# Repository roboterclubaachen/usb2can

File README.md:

# usb2can: Compact, isolated USB to CAN Adaptor <span style="float:right;"></span>

USB2CAN is a compact, USB-based and isolated CAN adaptor.

It is based on

 * STM32F072 Crystal-less STM32F072 ARM Cortex-M0 Processor
 * ADM3053 Isolated CAN Transceiver

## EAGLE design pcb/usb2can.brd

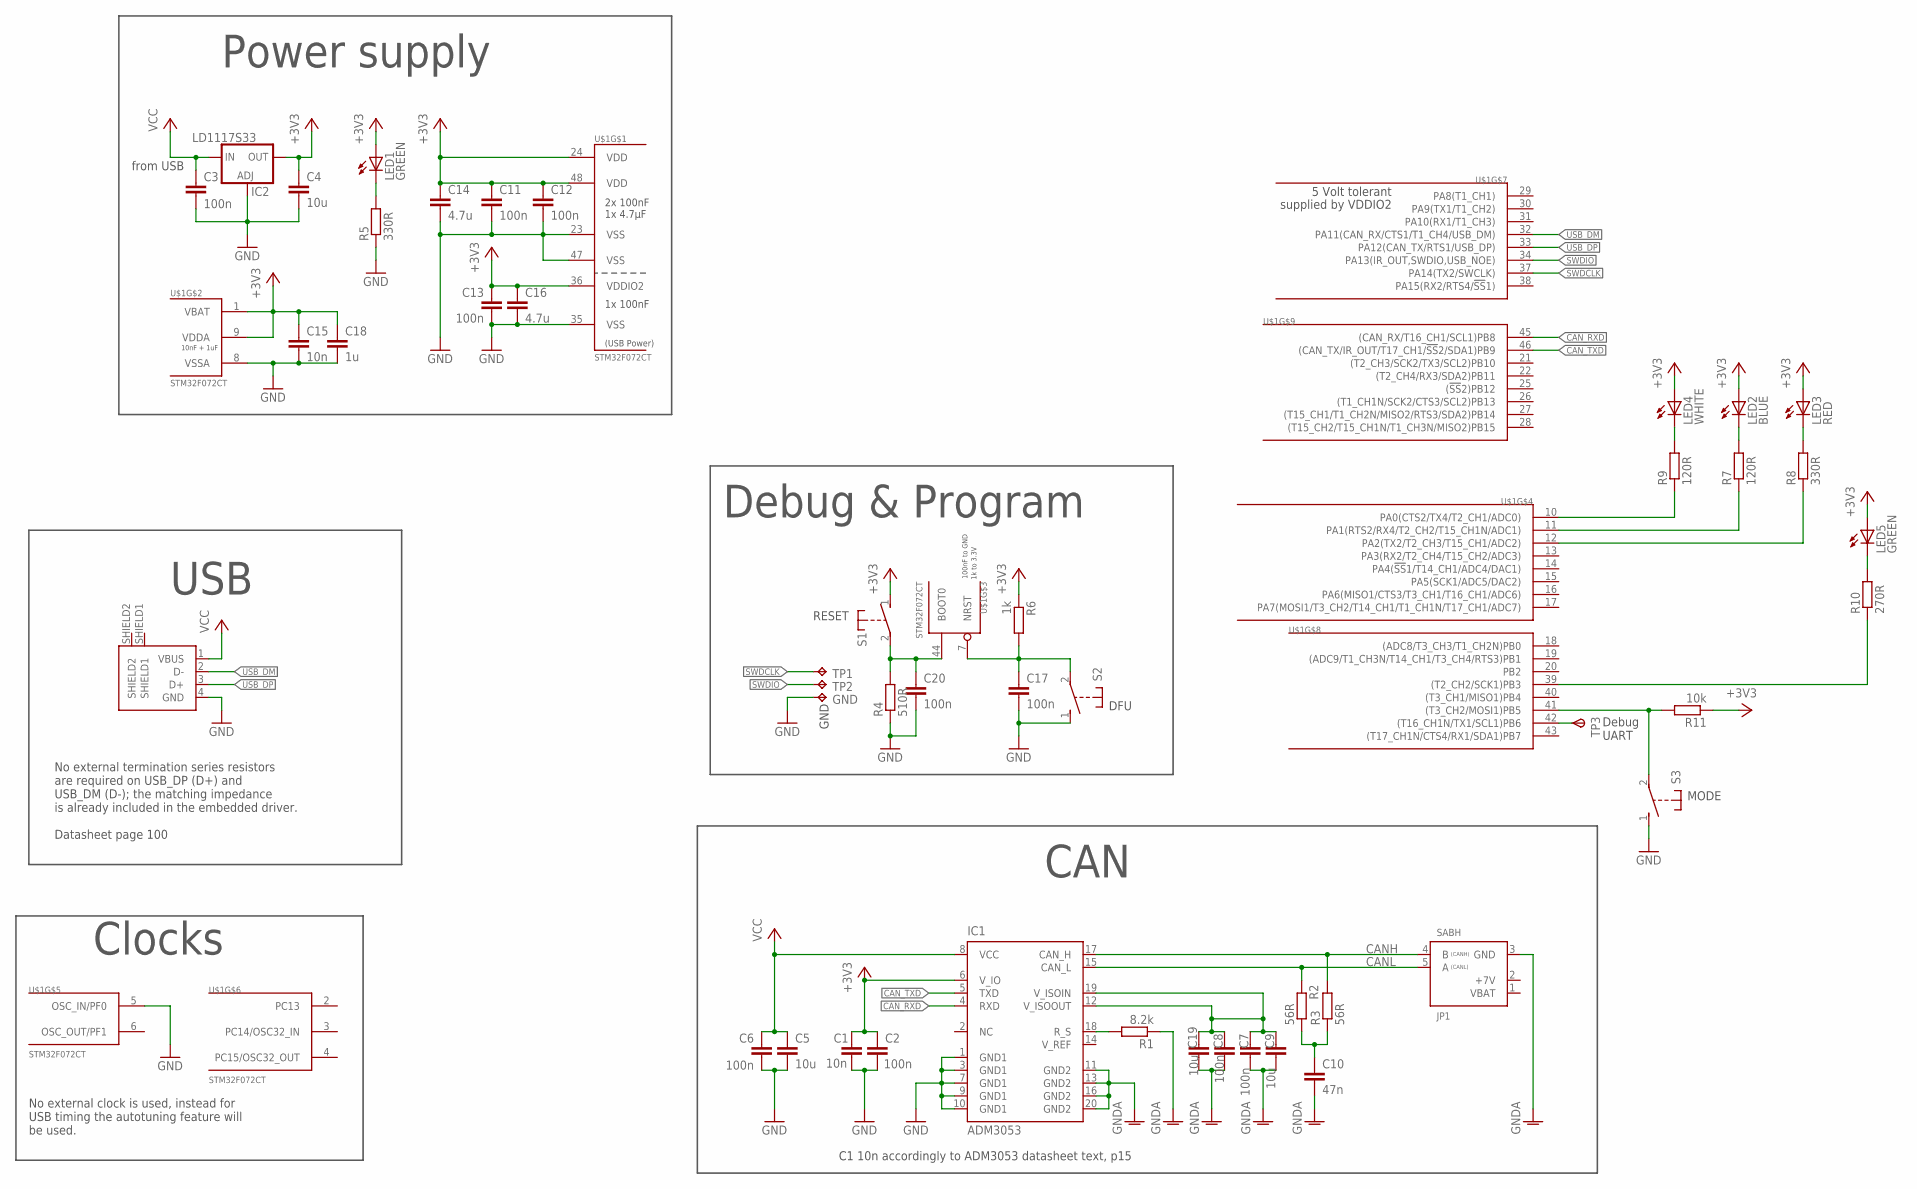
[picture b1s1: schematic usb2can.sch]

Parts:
C1: 10n; C0603K
C2, C3, C6: 100n; C0603K
C4, C5, C9, C19: 10u; C0805K
C7, C8: 100n; C0805K
C10: 47n; C0603K
C11, C12, C13, C17, C20: 100n; C0603
C14, C16: 4.7u; C0805K
C15: 10n; C0603
C18: 1u; C0805K
CON1: USB_A_MALESMD; USB_A_MALE_SMD
GND: TPB2,54; B2,54
IC1: ADM3053; SO20L
IC2: LD1117S33; SOT223
JP1: SABH; 7395-05
LED1, LED5: GREEN; CHIPLED_0603
LED2: BLUE; CHIPLED_0603
LED3: RED; CHIPLED_0603
LED4: WHITE; CHIPLED_0603
R1: 8.2k; R0603
R2, R3: 56R; R0805
R4: 510R; R0603
R5, R8: 330R; R0603
R6: 1k; R0603
R7, R9: 120R; R0603
R10: 270R; R0603
R11: 10k; R0603
S1, S2, S3: MICRO_SWITCH_3X6X2.5S; MICRO_SWITCH_3X6X2.5
TP1, TP2: TPB2,54; B2,54
TP3: TPSTP07R; TP07R
U$1: STM32F072CT; TQFP48

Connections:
+3V3: C1.1, C2.1, C4.1, C11.1, C12.1, C13.1, C14.1, C15.1, C16.1, C18.1, IC1.6 (V_IO), IC2.4 (OUT), LED1.A, LED2.A, LED3.A, LED4.A, LED5.A, R6.1, R11.1, S1.1, U$1.1 (VBAT), U$1.9 (VDDA), U$1.24 (VDD), U$1.36 (VDDIO2), U$1.48 (VDD)
CANH: IC1.17 (CAN_H), JP1.4 (B), R3.2
CANL: IC1.15 (CAN_L), JP1.5 (A), R2.2
CAN_RXD: IC1.4 (RXD), U$1.45 ((CAN_RX/T16_CH1/SCL1)PB8)
CAN_TXD: IC1.5 (TXD), U$1.46 ((CAN_TX/IR_OUT/T17_CH1/!SS!2/SDA1)PB9)
GND: C1.2, C2.2, C3.2, C4.2, C5.2, C6.2, C11.2, C12.2, C13.2, C14.2, C15.2, C16.2, C17.2, C18.2, C20.2, CON1.4 (GND), GND.TP, IC1.1 (GND1), IC1.3 (GND1), IC1.7 (GND1), IC1.9 (GND1), IC1.10 (GND1), IC2.1 (ADJ), R4.1, R5.1, S2.1, S3.1, U$1.5 (OSC_IN/PF0), U$1.8 (VSSA), U$1.23 (VSS), U$1.35 (VSS), U$1.47 (VSS)
GNDA: C7.2, C8.2, C9.2, C10.2, C19.2, IC1.11 (GND2), IC1.13 (GND2), IC1.16 (GND2), IC1.20 (GND2), JP1.3 (GND), R1.1
unnamed: IC1.18 (R_S), R1.2
unnamed: C10.1, R2.1, R3.1
unnamed: LED1.C, R5.2
unnamed: C20.1, R4.2, S1.2, U$1.44 (BOOT0)
unnamed: C17.1, R6.2, S2.2, U$1.7 (NRST)
unnamed: C7.1, C8.1, C9.1, C19.1, IC1.12 (V_ISOOUT), IC1.19 (V_ISOIN)
unnamed: LED2.C, R7.2
unnamed: R11.2, S3.2, U$1.41 ((T3_CH2/MOSI1)PB5)
unnamed: LED3.C, R8.2
unnamed: LED4.C, R9.2
unnamed: R9.1, U$1.10 (PA0(CTS2/TX4/T2_CH1/ADC0))
unnamed: R7.1, U$1.11 (PA1(RTS2/RX4/T2_CH2/T15_CH1N/ADC1))
unnamed: R8.1, U$1.12 (PA2(TX2/T2_CH3/T15_CH1/ADC2))
unnamed: LED5.C, R10.2
unnamed: R10.1, U$1.39 ((T2_CH2/SCK1)PB3)
SWDCLK: TP1.TP, U$1.37 (PA14(TX2/SWCLK))
SWDIO: TP2.TP, U$1.34 (PA13(IR_OUT,SWDIO,USB_NOE))
TX: TP3.TP, U$1.42 ((T16_CH1N/TX1/SCL1)PB6)
USB_DM: CON1.2 (D-), U$1.32 (PA11(CAN_RX/CTS1/T1_CH4/USB_DM))
USB_DP: CON1.3 (D+), U$1.33 (PA12(CAN_TX/RTS1/USB_DP))
VCC: C3.1, C5.1, C6.1, CON1.1 (VBUS), IC1.8 (VCC), IC2.3 (IN)

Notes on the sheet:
CAN
No external termination series resistors are required on USB_DP (D+) and USB_DM (D-); the matching impedance is already included in the embedded driver. Datasheet page 100
USB
Clocks
No external clock is used, instead for USB timing the autotuning feature will be used.
from USB
Power supply
Debug & Program
Debug UART
C1 10n accordingly to ADM3053 datasheet text, p15
DFU
RESET
MODE

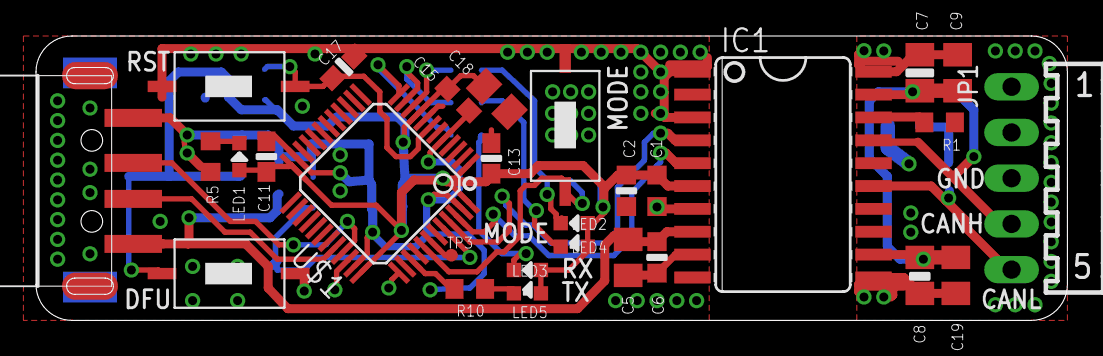
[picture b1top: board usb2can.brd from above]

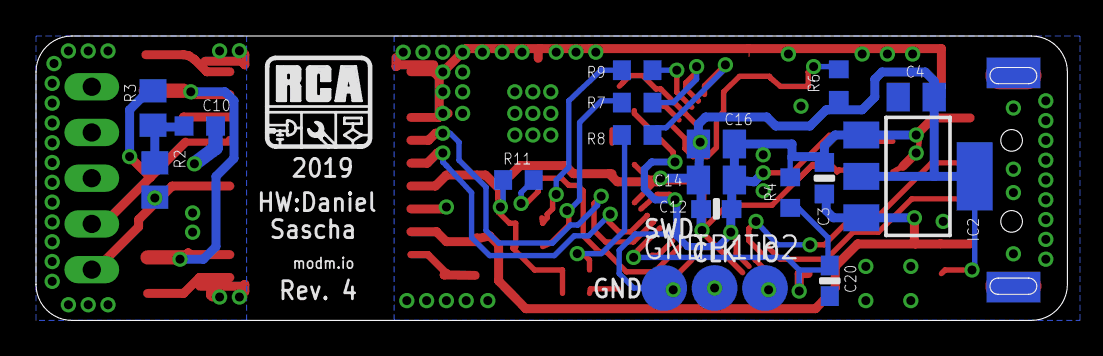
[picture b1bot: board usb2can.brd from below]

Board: 2 copper layers, 57.3 x 15.8 mm, 49 parts (19 on the bottom side), 28 nets.

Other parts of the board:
U$2: LOGO_SILK_BOT

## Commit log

2015-06-29 add Eagle lib for ADM3053
2015-06-29 add Eagle STM32 library
2015-06-29 add first schematic draft
2015-06-29 add gitignore
2015-06-29 add datasheets for ADM3053 and LD1117
2015-06-29 add Application Note for ADM3053 Evaluation Kit
2015-06-29 add README
2015-07-03 add STM32F072 datasheet and reference manual
2015-07-03 add some capacitors and connect USB and CAN
2015-07-03 add STM32F072 Discovery board manual
2015-07-05 schematic: clock done, USB needs no series-R, debug port done, power supply revised
2015-07-05 schematic: use another usb connector and add forgotten library
2015-12-21 progress made by Martin
2015-12-21 pcb: fix capacitor values for ADM3053
2015-12-22 pcb: final routing and small schamtic fixes
    * Testpad for UART TX
    * 4 User LEDs
    * 1 User Button
    * RCA CAN-connector
    * Bypass capacitor for BOOT0
2015-12-22 pcb: add GERBER export for OSHPARK
2015-12-22 final order of rev1
2016-01-07 pcb: update schematic with correct values
2016-01-11 add xpcc as submodule
2016-01-11 [tests] add blink test
2016-01-11 leds are low active => invert signals
2016-01-11 [tests] blink: use button
2016-01-11 [tests] add CAN test
2016-01-11 add udev rules file
2016-01-11 pcb: fix CAN transceiver V_ISOIN and V_ISOOUT not connected
2016-01-11 pcb: adapt resistor values for LEDs
2016-01-12 [tests] we only have a 48 pin controller
2017-01-20 pcb: increment revision and export for OSHPark
2017-01-20 pcb: add bottom pads for USB connector
2017-03-07 schematic: remove wire crossing between CAN_H and CAN_H.
2017-03-07 schematic: rename unnamed wires to CANH and CANL.
2017-03-07 schematic: Bypass Capacitors and Silk Screen
    - Bypass capacitors: nearest capacitor should be the smallest.
    - Add label to 100n capacitors
    - Add label to LEDs
2017-03-07 pcb: Create Rev3 Gerbers and save new viewport.
2017-08-25 Enable Travis CI.
2017-08-25 Update Readme and add TravisCI build status.
2017-08-25 Update xpcc submodule to 2017q2
2017-09-04 [tests] Get blinky running again.
    - Test 8 MHz clock with PLL.
    - Got hard faults when switching to 48 MHz clock because flash latency was not set at all
    - HSI48MHz clock is working reliably
    - Use common SConstruct from xpcc
    - Add Logger to board file
    - Add xpcc_abandon handler
2017-09-04 schematic: Add text to buttons.
2018-12-18 Add smaller package for CAN transceiver
2018-12-18 Update layout. Make easier to solder
2018-12-18 Ignore cam log files and library backups
2018-12-18 Add CAM job config
2018-12-18 pcb: Create Rev4 Gerbers
2019-10-29 pcb: Smash and place NAME and VALUE
